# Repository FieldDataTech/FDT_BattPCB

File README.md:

# FDT_BattPCB
Eagle CADsoft files for Battery PCB

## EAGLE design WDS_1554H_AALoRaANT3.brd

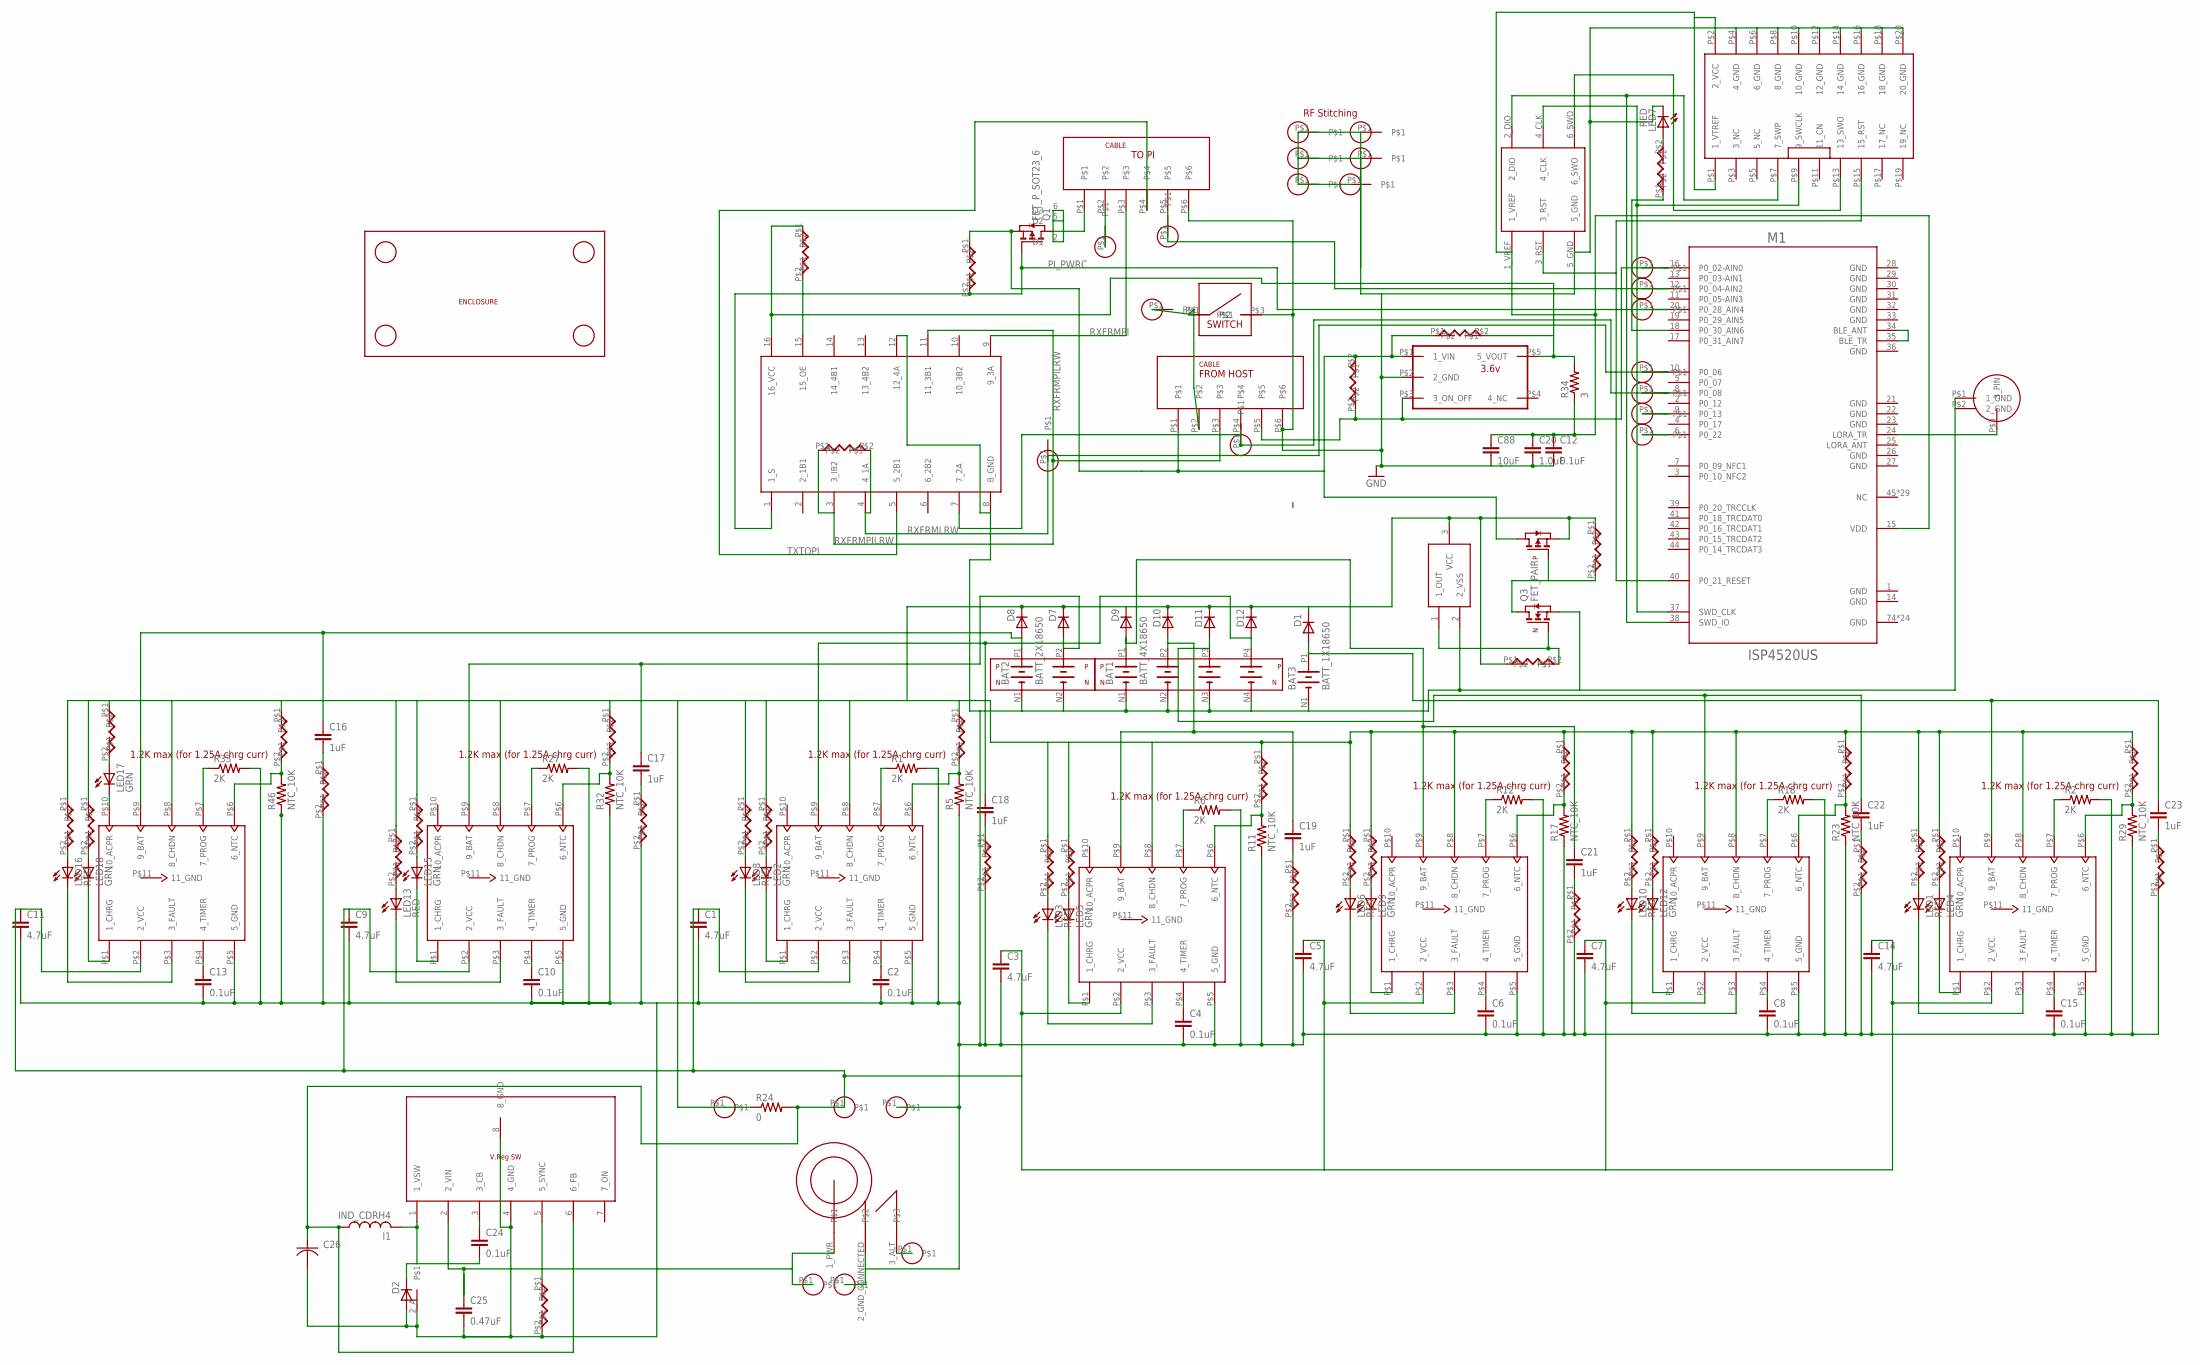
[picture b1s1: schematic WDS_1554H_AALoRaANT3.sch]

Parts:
BAT1: BATT_4X18650
BAT2: BATT_2X18650
BAT3: BATT_1X18650
BOX1: ENCL_1554H
C1, C3, C5, C7, C9, C11, C14: 4.7uF; C0603
C2, C4, C6, C8, C10, C12, C13, C15, C24: 0.1uF; C0402
C16, C17, C18, C19, C21, C22, C23: 1uF; C0603
C20: 1.0uF; C0603
C25: 0.47uF; C0402
C26: CAP_1210; C1210K
C88: 10uF; C0603
D1, D7, D8, D9, D10, D11, D12: DIODE_SCHTKY; SOD323
D2: DIODE_BIG
G2: GPS_ANT; GPS_ANTE
I1: IND_CDRH4; IND_CDRH4D
J1, J5: CONN_6P_VERT; CONN_6PCABLE
J2: HDR_JLINK
J3: HDR_SEGER_6P; HDR_SEGGER_6P
LED1, LED3, LED6, LED7, LED8, LED10, LED13, LED16: RED; CHIP-LED0603
LED2, LED4, LED5, LED9, LED12, LED15, LED17, LED18: GRN; CHIP-LED0603
M1: ISP4520US; ISP4520-LGA-QFN74-9.8X17.2X1.7MM
Q1: FET_P_SOT23_6; SOT23-6
Q3: FET_PAIR; SSOT6
R1, R2, R6, R12, R18, R27, R33: 2K; SMD_0402
R3, R7, R8, R9, R13, R14, R15, R19, R21, R28, R30, R35, R36, R37, R45, R53, R65: 1K; SMD_0402
R4, R10, R16, R20, R22, R31, R38: 4k; SMD_0402
R5, R11, R17, R23, R29, R32, R46: NTC_10K; R0603
R24: 0; SMD_0402
R25, R26, R42, R43: 1M; SMD_0402
R34: 3; R0402
R39, R47, R48, R49, R50, R51, R52: 1ohm; SMD_0402
R40, R44: DNS_0; SMD_0402
R41: DNS_100K; SMD_0402
TP1, TP6, TP7, TP8, TP9, TP10, TP11, TP12, TP13, TP15, TP16, TP17, TP18, TP19, TP20, TP21, TP22, TP23: TP_26AWG
TP2, TP3, TP4, TP5, TP14, TP24: TP_THSM2
U1, U2, U3, U4, U5, U8, U10: LTC4053
U6: 3.6v; SOT_235B
U7: VOLT_SUPR; TO236
U9: MUX_2X_1_2; TSSOP16
U11: VREG_SW_LM2677; TO263-7
U$1: SWITCH
U$2: CONN_BARREL_SMHOLE; CONN_JACK_VERT_SMHOLE

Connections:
GND: BAT1.N1, BAT1.N2, BAT1.N3, BAT1.N4, BAT2.N1, BAT2.N2, BAT3.N1 (-), C1.2, C2.2, C3.2, C4.2, C5.2, C6.2, C7.2, C8.2, C9.2, C10.2, C11.2, C12.2, C13.2, C14.2, C15.2, C20.2, C25.2, C26.2 (2N), C88.2, D2.1_A (A), D2.2_A, G2.P$1 (1_GND), G2.P$2 (2_GND), J1.P$6, J2.P$4 (4_GND), J2.P$6 (6_GND), J2.P$8 (8_GND), J2.P$10 (10_GND), J2.P$12 (12_GND), J2.P$14 (14_GND), J2.P$16 (16_GND), J2.P$18 (18_GND), J2.P$20 (20_GND), J3.5_GND, J5.P$6, LED7.C, M1.1 (GND), M1.14 (GND), M1.21 (GND), M1.22 (GND), M1.23 (GND), M1.26 (GND), M1.27 (GND), M1.28 (GND), M1.29 (GND), M1.30 (GND), M1.31 (GND), M1.32 (GND), M1.33 (GND), M1.36 (GND), M1.74 (GND), M1.75 (GND), M1.76 (GND), M1.77 (GND), M1.78 (GND), M1.79 (GND), M1.80 (GND), M1.81 (GND), M1.82 (GND), M1.83 (GND), M1.84 (GND), M1.85 (GND), M1.86 (GND), M1.87 (GND), M1.88 (GND), M1.89 (GND), M1.90 (GND), M1.91 (GND), M1.92 (GND), M1.93 (GND), M1.94 (GND), M1.95 (GND), M1.96 (GND), M1.97 (GND), Q3.5 (N_S), R1.P$2 (2), R2.P$2 (2), R5.1, R6.P$2 (2), R11.1, R12.P$2 (2), R17.1, R18.P$2 (2), R23.1, R27.P$2 (2), R29.1, R32.1, R33.P$2 (2), R39.P$2, R46.1, R47.P$2, R48.P$2, R49.P$2, R50.P$2, R51.P$2, R52.P$2, R53.P$2, TP3.P$1, TP8.P$1, TP15.P$1, TP16.P$1, TP17.P$1, TP18.P$1, TP19.P$1, TP24.P$1, U1.P$5 (5_GND), U2.P$5 (5_GND), U3.P$5 (5_GND), U4.P$5 (5_GND), U5.P$5 (5_GND), U6.P$2 (2_GND), U7.2 (2_VSS), U8.P$5 (5_GND), U9.8 (8_GND), U9.12 (12_4A), U10.P$5 (5_GND), U11.4 (4_GND), U11.8 (8_GND), U$1.P$3, U$2.2_GND_CONNECTED
LORA_ANT: M1.25 (LORA_ANT)
LTE_RESET_X: J1.P$2, TP1.P$1, U$1.P$1
unnamed: R53.P$1, U11.5 (5_SYNC)
unnamed: BAT1.P1, C21.1, D9.2_A (A), U4.P$9 (9_BAT)
unnamed: C15.1, U10.P$4 (4_TIMER)
unnamed: R2.P$1 (1), U10.P$7 (7_PROG)
unnamed: LED1.A, R8.P$2
unnamed: J1.P$5, M1.16 (P0_02-AIN0), R41.P$1, TP11.P$1, U6.P$3 (3_ON_OFF)
unnamed: Q3.1 (N_G), R26.P$2, U7.1 (1_OUT)
unnamed: J1.P$1, Q1.4 (S), Q3.4 (P_D), R40.P$1, R41.P$2, R42.P$1, U6.P$1 (1_VIN)
unnamed: C24.1, U11.3 (3_CB)
unnamed: C16.2, R39.P$1
unnamed: Q3.3 (P_G), Q3.6 (N_D), R25.P$2
unnamed: BAT1.P2, C19.1, D10.2_A (A), U3.P$9 (9_BAT)
unnamed: BAT1.P4, C18.1, D12.2_A (A), U1.P$9 (9_BAT)
unnamed: C1.1, C3.1, C5.1, C7.1, C9.1, C11.1, C14.1, C26.1 (1P), I1.P$3 (1), R24.P$2 (2), TP2.P$1, U1.P$2 (2_VCC), U2.P$2 (2_VCC), U3.P$2 (2_VCC), U4.P$2 (2_VCC), U5.P$2 (2_VCC), U8.P$2 (2_VCC), U10.P$2 (2_VCC), U11.6 (6_FB)
unnamed: LED7.A, R45.P$2
unnamed: TP5.P$1, U$2.3_ALT
unnamed: C2.1, U1.P$4 (4_TIMER)
unnamed: LED4.A, R14.P$2
unnamed: R1.P$1 (1), U1.P$7 (7_PROG)
unnamed: LED2.A, R3.P$2
unnamed: LED4.C, U10.P$1 (1_CHRG)
unnamed: LED2.C, U1.P$1 (1_CHRG)
unnamed: LED8.C, U1.P$3 (3_FAULT)
unnamed: R4.P$2, R5.2, U1.P$6 (6_NTC)
unnamed: BAT2.P2, C17.1, D7.2_A (A), U2.P$9 (9_BAT)
unnamed: LED1.C, U10.P$3 (3_FAULT)
unnamed: C4.1, U3.P$4 (4_TIMER)
unnamed: R6.P$1 (1), U3.P$7 (7_PROG)
unnamed: LED3.A, R7.P$2
unnamed: R20.P$2, R29.2, U10.P$6 (6_NTC)
unnamed: LED5.A, R9.P$2
unnamed: C17.2, R47.P$1
unnamed: LED5.C, U3.P$1 (1_CHRG)
unnamed: LED3.C, U3.P$3 (3_FAULT)
unnamed: R10.P$2, R11.2, U3.P$6 (6_NTC)
unnamed: C10.1, U2.P$4 (4_TIMER)
unnamed: C6.1, U4.P$4 (4_TIMER)
unnamed: R12.P$1 (1), U4.P$7 (7_PROG)
unnamed: LED6.A, R13.P$2
unnamed: BAT2.P1, C16.1, D8.2_A (A), U8.P$9 (9_BAT)
unnamed: LED9.A, R15.P$2
unnamed: C12.1, C20.1, C88.1, J2.P$1 (1_VTREF), J2.P$2 (2_VCC), J3.1_VREF, M1.15 (VDD), R34.1
unnamed: LED9.C, U4.P$1 (1_CHRG)
unnamed: LED6.C, U4.P$3 (3_FAULT)
unnamed: R16.P$2, R17.2, U4.P$6 (6_NTC)
unnamed: R43.P$2, U9.15 (15_OE)
unnamed: R27.P$1 (1), U2.P$7 (7_PROG)
unnamed: LED13.A, R28.P$2
unnamed: C8.1, U5.P$4 (4_TIMER)
unnamed: R18.P$1 (1), U5.P$7 (7_PROG)
unnamed: LED10.A, R19.P$2
unnamed: C18.2, R48.P$1
unnamed: LED12.A, R21.P$2
unnamed: C19.2, R49.P$1
unnamed: LED12.C, U5.P$1 (1_CHRG)
unnamed: LED10.C, U5.P$3 (3_FAULT)
unnamed: R22.P$2, R23.2, U5.P$6 (6_NTC)
unnamed: J2.P$13 (13_SWO), J3.6_SWO
unnamed: LED15.A, R30.P$2
unnamed: LED15.C, U2.P$1 (1_CHRG)
unnamed: LED13.C, U2.P$3 (3_FAULT)
unnamed: R31.P$2, R32.2, U2.P$6 (6_NTC)
unnamed: C21.2, R50.P$1
unnamed: BAT1.P3, C22.1, D11.2_A (A), U5.P$9 (9_BAT)
unnamed: C13.1, U8.P$4 (4_TIMER)
unnamed: R33.P$1 (1), U8.P$7 (7_PROG)
unnamed: LED16.A, R35.P$2
unnamed: LED17.A, R36.P$2
unnamed: LED18.A, R37.P$2
unnamed: LED17.C, U8.P$10 (10_ACPR)
unnamed: LED18.C, U8.P$1 (1_CHRG)
unnamed: LED16.C, U8.P$3 (3_FAULT)
unnamed: R38.P$2, R46.2, U8.P$6 (6_NTC)
unnamed: LED8.A, R65.P$2
unnamed: M1.34 (BLE_ANT), M1.35 (BLE_TR)
unnamed: J2.P$15 (15_RST), J3.3_RST, M1.40 (P0_21_RESET)
unnamed: J2.P$7 (7_SWP), J3.2_DIO, M1.38 (SWD_IO)
unnamed: J2.P$9 (9_SWCLK), J3.4_CLK, M1.37 (SWD_CLK)
unnamed: J5.P$1, Q1.1 (D), Q1.2 (D1), Q1.5 (D2), Q1.6 (D3)
unnamed: R34.2, R40.P$2, R43.P$1, U6.P$5 (5_VOUT), U9.16 (16_VCC)
unnamed: C22.2, R51.P$1
unnamed: G2.P$3 (3_PIN), M1.24 (LORA_TR)
unnamed: M1.18 (P0_30_AIN6), R45.P$1
unnamed: J5.P$2, TP20.P$1
unnamed: J5.P$5, M1.12 (P0_04-AIN2), TP12.P$1, TP21.P$1
unnamed: M1.9 (P0_13), TP9.P$1
unnamed: M1.6 (P0_22), TP10.P$1
unnamed: BAT3.P1 (+), C23.1, D1.2_A (A), U10.P$9 (9_BAT)
unnamed: C23.2, R52.P$1
unnamed: C24.2, D2.3_K (K), I1.P$4 (2), U11.1 (1_VSW)
unnamed: C25.1, TP14.P$1, U11.2 (2_VIN), U$2.1_PWR
PI_PWRC: M1.20 (P0_28_AIN4), Q1.3 (G), R42.P$2, TP13.P$1, U9.1 (1_S)
RXFRMLRW: M1.10 (P0_06), R44.P$2, TP6.P$1, TP22.P$1, U9.4 (4_1A)
RXFRMPI: J5.P$3, U9.9 (9_3A)
RXFRMPILRW: J1.P$3, R44.P$1, U9.3 (3_IB2), U9.11 (11_3B1)
TXTOLRW: J1.P$4, M1.8 (P0_08), TP7.P$1, TP23.P$1, U9.7 (7_2A)
TXTOPI: J5.P$4, U9.5 (5_2B1)
VCC1: D1.1_K (K), D7.1_K (K), D8.1_K (K), D9.1_K (K), D10.1_K (K), D11.1_K (K), D12.1_K (K), Q3.2 (P_S), R3.P$1, R4.P$1, R7.P$1, R8.P$1, R9.P$1, R10.P$1, R13.P$1, R14.P$1, R15.P$1, R16.P$1, R19.P$1, R20.P$1, R21.P$1, R22.P$1, R24.P$1 (1), R25.P$1, R26.P$1, R28.P$1, R30.P$1, R31.P$1, R35.P$1, R36.P$1, R37.P$1, R38.P$1, R65.P$1, TP4.P$1, U1.P$8 (8_CHDN), U2.P$8 (8_CHDN), U3.P$8 (8_CHDN), U4.P$8 (8_CHDN), U5.P$8 (8_CHDN), U7.3 (VCC), U8.P$8 (8_CHDN), U10.P$8 (8_CHDN)

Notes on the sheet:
1.2K max (for 1.25A chrg curr)
3.6v
RF Stitching
TO PI
FROM HOST

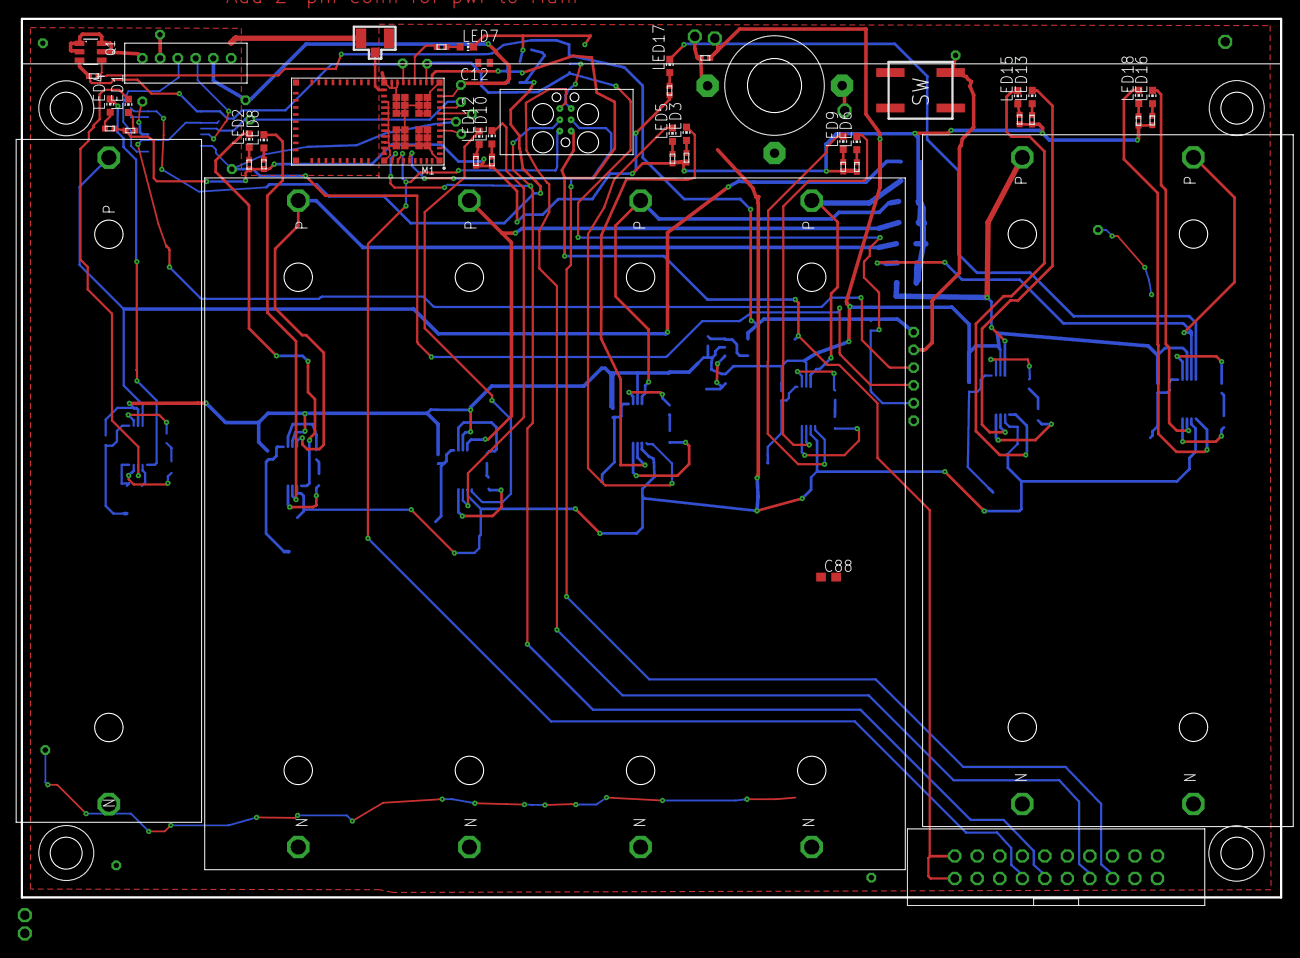
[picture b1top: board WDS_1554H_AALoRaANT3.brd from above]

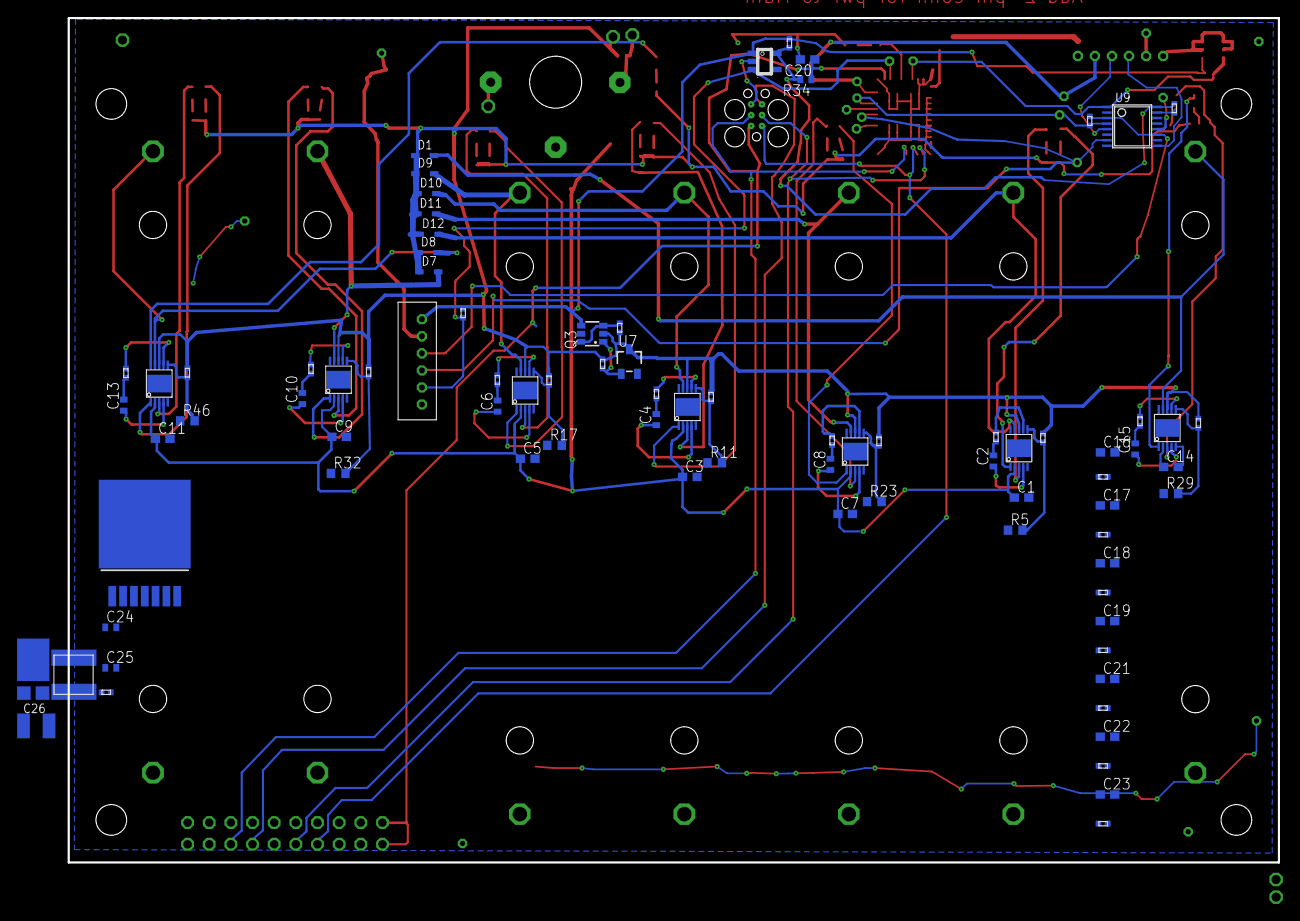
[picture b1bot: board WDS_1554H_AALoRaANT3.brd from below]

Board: 2 copper layers, 142.0 x 99.1 mm, 155 parts (83 on the bottom side), 100 nets.

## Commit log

2021-04-23 Original commit of battery/LRW board files.

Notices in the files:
parts and their libraries:
InSight_SiP_ISP4520xx: Copyright (c)2019, All Rights Reserved.
